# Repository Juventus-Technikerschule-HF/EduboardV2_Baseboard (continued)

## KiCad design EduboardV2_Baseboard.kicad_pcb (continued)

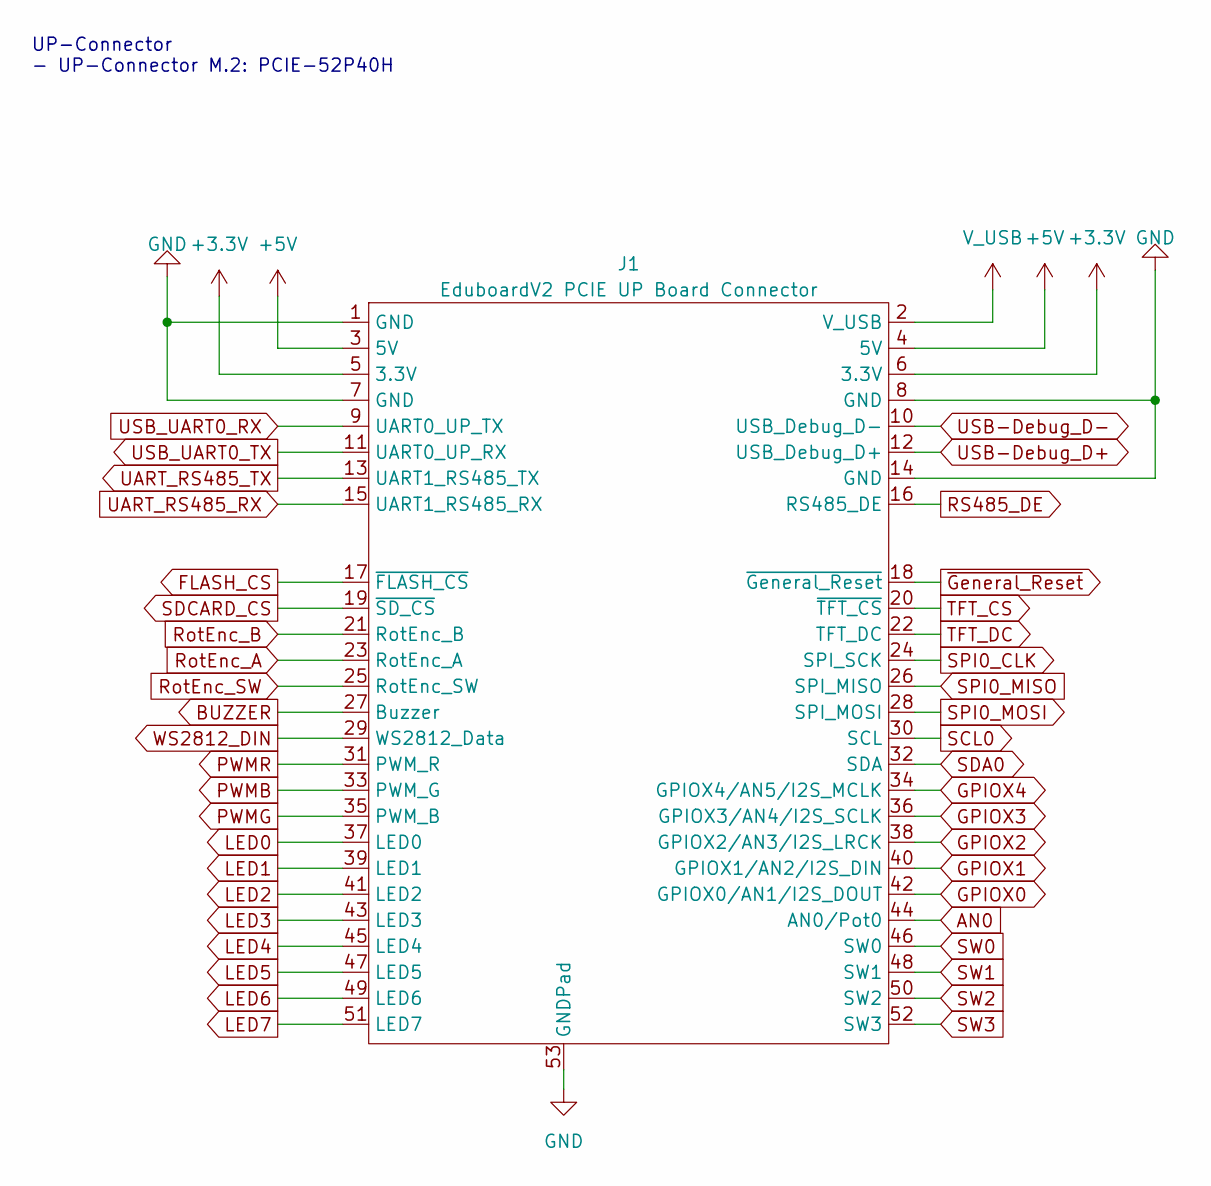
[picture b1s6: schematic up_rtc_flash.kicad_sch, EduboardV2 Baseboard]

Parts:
J1: EduboardV2 PCIE UP Board Connector; CONN-SMD_52P-P0.80-V_91304-70-052RXXX

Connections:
+5V: J1.3 (5V), J1.4 (5V); also elsewhere on the board
AN0: J1.44 (AN0/Pot0); also elsewhere on the board
BUZZER: J1.27 (Buzzer); also elsewhere on the board
FLASH_CS: J1.17 (~FLASH_CS); also elsewhere on the board
GPIOX0: J1.42 (GPIOX0/AN1/I2S_DOUT); also elsewhere on the board
GPIOX1: J1.40 (GPIOX1/AN2/I2S_DIN); also elsewhere on the board
GPIOX2: J1.38 (GPIOX2/AN3/I2S_LRCK); also elsewhere on the board
GPIOX3: J1.36 (GPIOX3/AN4/I2S_SCLK); also elsewhere on the board
GPIOX4: J1.34 (GPIOX4/AN5/I2S_MCLK); also elsewhere on the board
LED0: J1.37 (LED0); also elsewhere on the board
LED1: J1.39 (LED1); also elsewhere on the board
LED2: J1.41 (LED2); also elsewhere on the board
LED3: J1.43 (LED3); also elsewhere on the board
LED4: J1.45 (LED4); also elsewhere on the board
LED5: J1.47 (LED5); also elsewhere on the board
LED6: J1.49 (LED6); also elsewhere on the board
LED7: J1.51 (LED7); also elsewhere on the board
PWMB: J1.33 (PWM_G); also elsewhere on the board
PWMG: J1.35 (PWM_B); also elsewhere on the board
PWMR: J1.31 (PWM_R); also elsewhere on the board
RS485_DE: J1.16 (RS485_DE); also elsewhere on the board
RotEnc_A: J1.23 (RotEnc_A); also elsewhere on the board
RotEnc_B: J1.21 (RotEnc_B); also elsewhere on the board
RotEnc_SW: J1.25 (RotEnc_SW); also elsewhere on the board
SCL0: J1.30 (SCL); also elsewhere on the board
SDA0: J1.32 (SDA); also elsewhere on the board
SDCARD_CS: J1.19 (~SD_CS); also elsewhere on the board
SPI0_MISO: J1.26 (SPI_MISO); also elsewhere on the board
SPI0_MOSI: J1.28 (SPI_MOSI); also elsewhere on the board
SW0: J1.46 (SW0); also elsewhere on the board
SW1: J1.48 (SW1); also elsewhere on the board
SW2: J1.50 (SW2); also elsewhere on the board
SW3: J1.52 (SW3); also elsewhere on the board
TFT_CS: J1.20 (~TFT_CS); also elsewhere on the board
TFT_DC: J1.22 (TFT_DC); also elsewhere on the board
UART_RS485_RX: J1.15 (UART1_RS485_RX); also elsewhere on the board
UART_RS485_TX: J1.13 (UART1_RS485_TX); also elsewhere on the board
USB-Debug_D+: J1.12 (USB_Debug_D+); also elsewhere on the board
USB-Debug_D-: J1.10 (USB_Debug_D-); also elsewhere on the board
USB_UART0_TX: J1.11 (UART0_UP_RX); also elsewhere on the board
V_USB: J1.2 (V_USB); also elsewhere on the board
WS2812_DIN: J1.29 (WS2812_Data); also elsewhere on the board
~General_Reset: J1.18 (~General_Reset); also elsewhere on the board

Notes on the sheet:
UP-Connector - UP-Connector M.2: PCIE-52P40H

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
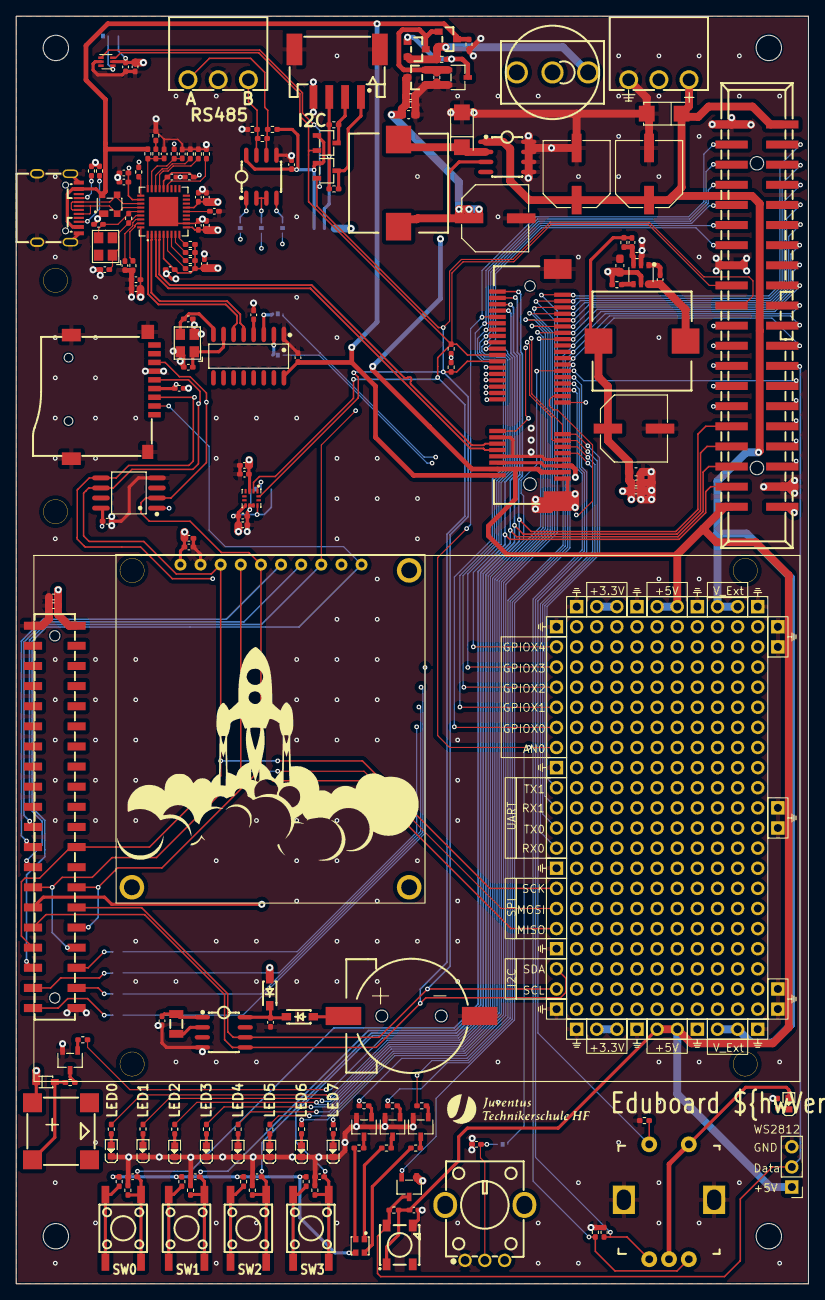
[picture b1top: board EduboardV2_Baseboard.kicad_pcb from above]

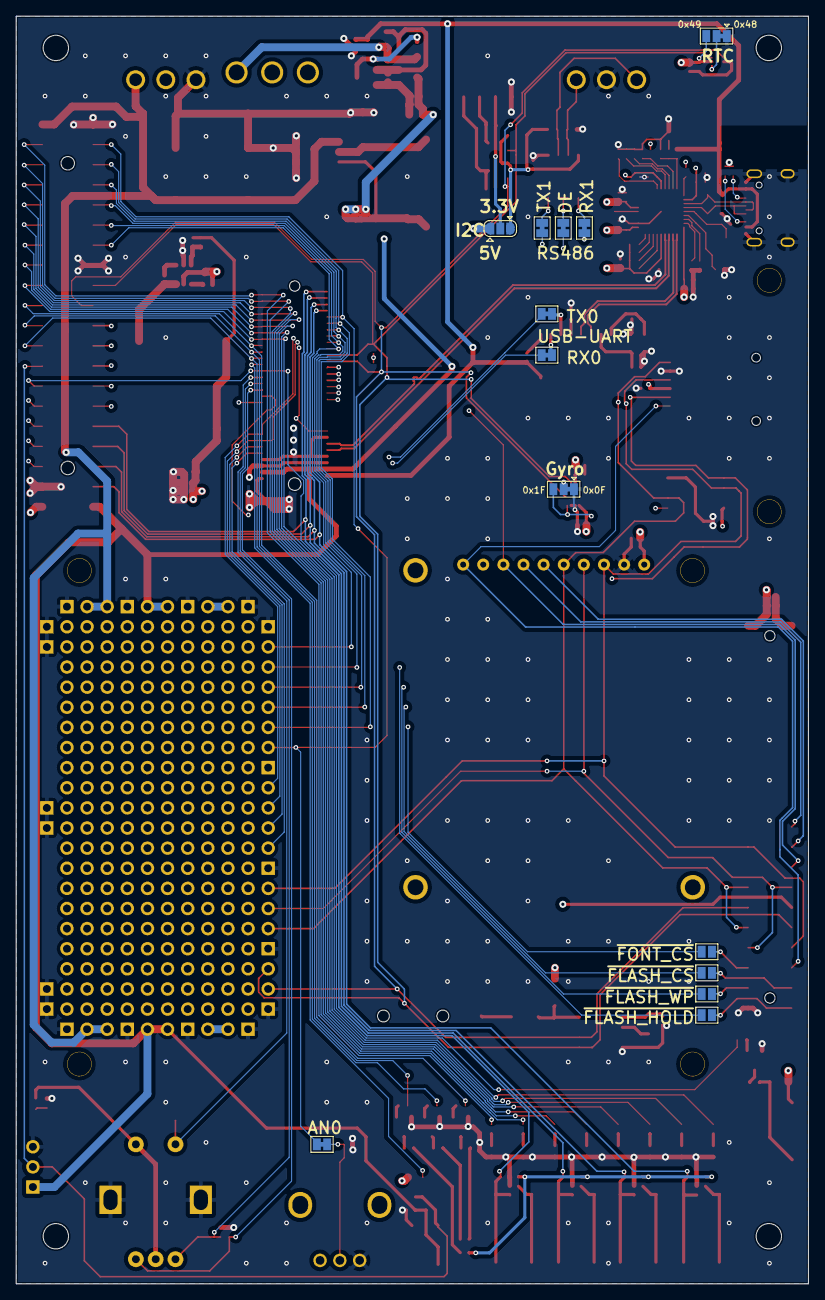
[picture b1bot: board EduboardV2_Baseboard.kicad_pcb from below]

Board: 4 copper layers, 100.0 x 160.0 mm, 189 parts (13 on the bottom side), 129 nets.

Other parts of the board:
C33, C35, C37, C39, C47, C49, C51, C53, C55: 100nF; C_0402_1005Metric_Pad0.74x0.62mm_HandSolder
C34, C36, C38, C40, C48, C50, C52, C54, C56: 1uF; C_0402_1005Metric_Pad0.74x0.62mm_HandSolder
JP9: SolderJumper_2_Bridged; SolderJumper-2_P1.3mm_Bridged_Pad1.0x1.5mm
T4, T7, T8: AO3400A; SOT-23-3_L2.9-W1.6-P1.90-LS2.8-BR
X1: 32.768 kHz; FC-135R_L3.2-W1.5

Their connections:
AN0: JP9.2 (B); also elsewhere on the board
unnamed 80: T7.3 (D); also elsewhere on the board
unnamed 81: T8.3 (D); also elsewhere on the board
SCL0: T7.2 (S); also elsewhere on the board
SDA0: T8.2 (S); also elsewhere on the board
WS2812_DIN: T4.2 (S); also elsewhere on the board
WS2812_DOUT: T4.3 (D); also elsewhere on the board

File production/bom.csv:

Designator,Footprint,Quantity,Value,LCSC Part #
BUZZER2,BUZ-SMD_4P-L8.5-W8.5-P8.50-BR,1,MLT-8530,
C1,0402,1,10pF,CL05C100JB5NNNC
C10,0603,1,"10uF, X5R, 25V",CL10A106MA8NRNC
C11,0402,1,"100nF, 50V",CL05B104KB54PNC
C12,0402,1,"1uF, 25V",CL05A105KA5NQNC
C13,0603,1,"10uF, X5R, 25V",CL10A106MA8NRNC
C14,0402,1,"100nF, 50V",CL05B104KB54PNC
C15,0402,1,"1uF, 25V",CL05A105KA5NQNC
"C16, C21, C5, C9",CAP-SMD_BD8.0-L8.3-W8.3-RD,4,"220uF, 35V",VEJ221M1VTR-0810
C17,0402,1,1nF,0402B102K500NT
C18,0402,1,10nF,CL05B103KB5NNNC
C19,0402,1,100nF,CL05B104KB54PNC
C2,0402,1,1uF,CL05A105KA5NQNC
C20,0402,1,10nF,CL05B103KB5NNNC
C22,0402,1,10nF,CL05B103KB5NNNC
C23,0402,1,100nF,CL05B104KB54PNC
C24,0402,1,10nF,CL05B103KB5NNNC
C25,0402,1,100nF,CL05B104KB54PNC
C26,0402,1,1uF,CL05A105KA5NQNC
C27,0402,1,1uF,CL05A105KA5NQNC
C28,0402,1,"100nF, 50V",CL05B104KB54PNC
C29,0402,1,22pF,0402CG220J500NT
C3,0402,1,10nF,CL05B103KB5NNNC
C30,0402,1,22pF,0402CG220J500NT
C31,0402,1,100nF,CL05B104KB54PNC
C32,0402,1,"100nF, 50V",CL05B104KB54PNC
C33,0402,1,100nF,CL05B104KB54PNC
C34,0402,1,1uF,CL05A105KA5NQNC
C35,0402,1,100nF,CL05B104KB54PNC
C36,0402,1,1uF,CL05A105KA5NQNC
C37,0402,1,100nF,CL05B104KB54PNC
C38,0402,1,1uF,CL05A105KA5NQNC
C39,0402,1,100nF,CL05B104KB54PNC
C4,0402,1,100nF,CL05B104KB54PNC
C40,0402,1,1uF,CL05A105KA5NQNC
C41,0402,1,"100nF, 50V",CL05B104KB54PNC
C42,0402,1,CL05C100JB5NNNC,CL05C100JB5NNNC
C43,0402,1,"100nF, 50V",CL05B104KB54PNC
C44,0402,1,CL05C100JB5NNNC,CL05C100JB5NNNC
C45,0402,1,"100nF, 50V",CL05B104KB54PNC
C46,0402,1,"100nF, 50V",CL05B104KB54PNC
C47,0402,1,100nF,CL05B104KB54PNC
C48,0402,1,1uF,CL05A105KA5NQNC
C49,0402,1,100nF,CL05B104KB54PNC
C50,0402,1,1uF,CL05A105KA5NQNC
C51,0402,1,100nF,CL05B104KB54PNC
C52,0402,1,1uF,CL05A105KA5NQNC
C53,0402,1,100nF,CL05B104KB54PNC
C54,0402,1,1uF,CL05A105KA5NQNC
C55,0402,1,100nF,CL05B104KB54PNC
C56,0402,1,1uF,CL05A105KA5NQNC
C6,0402,1,"100nF, 50V",CL05B104KB54PNC
C7,0603,1,"10uF, X5R, 25V",CL10A106MA8NRNC
C8,0402,1,22pF,0402CG220J500NT
"D1, D2",SOD-123_L2.7-W1.6-LS3.7-RD-1,2,B5819W_C8598,B5819W_C8598
"D10, D11, D12, D13, D5, D6, D7, D8, D9",LED0603-FD_BLUE,9,blue,19-217/BHC-ZL1M2RY/3T
D14,LED-SMD_FM-B2020RGBA-HG,1,RGB-LED,FM-B2020RGBA-HG
D15,LED-SMD_4P-L5.0-W5.0-TL_WS2812B-B,1,WS2812B-B_W,WS2812B-B/W
D16,SOD-323_L1.8-W1.3-LS2.5-RD,1,1N4148WST4,1N4148WS T4
D17,SOT-143-4_L2.9-W1.3-P1.92-LS2.4-BL,1,PRTR5V0U2X_C2827688,
"D3, D4",SMA_L4.3-W2.6-LS5.2-RD,2,SS210,SS210
IC1,SOIC-8_L5.0-W4.0-P1.27-LS6.0-BL,1,"PCF8563T_5,518","PCF8563T/5,518"
IC10,TQFN-36_L6.0-W6.0-P0.50-BL-EP3.7,1,USB2514BI-AEZG-TR,USB2514BI-AEZG-TR
IC2,SOIC-8_L5.3-W5.3-P1.27-LS8.0-BL,1,W25Q128JVSIQTR,W25Q128JVSIQTR
IC3,SOIC-8_L5.0-W4.0-P1.27-LS6.0-BL,1,XL1509-5.0E1,XL1509-5.0E1
IC4,TSOT-23-6_L2.9-W1.6-P0.95-LS2.8-BR,1,SY8113BADC,SY8113BADC
IC5,SOIC-8_L5.0-W4.0-P1.27-LS6.0-BL,1,SP3485EN-L_TR,SP3485EN-L/TR
IC8,LGA-12_L2.0-W2.0-P0.50-TR,1,STK8321,STK8321
J1,CONN-SMD_52P-P0.80-V_91304-70-052RXXX,1,EduboardV2 PCIE UP Board Connector,
JP1,SolderJumper-3_P1.3mm_Open_RoundedPad1.0x1.5mm,1,Stemma Voltage Selector,
"JP10, JP11, JP12, JP13",SolderJumper-2_P1.3mm_Open_Pad1.0x1.5mm,4,SolderJumper_2_Open,
"JP2, JP3",SolderJumper-3_P1.3mm_Bridged12_Pad1.0x1.5mm,2,SolderJumper_3_Bridged12,
"JP4, JP5, JP6, JP7, JP8, JP9",SolderJumper-2_P1.3mm_Bridged_Pad1.0x1.5mm,6,SolderJumper_2_Bridged,
"L1, L2",IND-SMD_L12.5-W12.5_SLF12565T,2,SLF12565T-680M2R0-PF,
"Q1, Q3, Q4",SOT-23_L2.9-W1.3-P1.90-LS2.4-BR,3,AO3401A,AO3401A
"Q2, T1, T2, T3, T4, T5, T7, T8",SOT-23-3_L2.9-W1.6-P1.90-LS2.8-BR,8,AO3400A,AO3400A
R1,0402,1,10k,0402WGF100JTCE
R10,0402,1,1k,0402WGF1001TCE
R11,0402,1,10k,0402WGF1002TCE
R12,0402,1,1k,0402WGF1001TCE
R13,RES-TH_RK09K1130AAU,1,50k,RK09K1130ACL
R14,0402,1,1k,0402WGF1001TCE
R15,0402,1,1k,0402WGF1001TCE
R16,0402,1,1k,0402WGF1001TCE
R17,0402,1,1k,0402WGF1001TCE
R18,0402,1,10k,0402WGF1002TCE
R19,0402,1,1k,0402WGF1001TCE
R2,0402,1,10k,0402WGF100JTCE
R21,0402,1,1k,0402WGF1001TCE
R22,0402,1,1k,0402WGF1001TCE
R23,0402,1,1k,0402WGF1001TCE
R25,0402,1,1k,0402WGF1001TCE
R26,0402,1,10k,0402WGF1002TCE
R27,0402,1,150R,0402WGF1500TCE
R28,0402,1,150R,0402WGF1500TCE
R29,0402,1,1k,0402WGF1001TCE
R3,0402,1,1M,0402WGF1003TCE
R30,0402,1,10k,0402WGF1002TCE
R31,0402,1,150R,0402WGF1500TCE
R32,0402,1,10R,0402WGF100JTCE
R33,0402,1,10R,0402WGF100JTCE
R34,0402,1,10R,0402WGF100JTCE
R35,0402,1,10k,0402WGF100JTCE
R36,0402,1,10k,0402WGF100JTCE
R37,0402,1,10k,0402WGF100JTCE
R38,0402,1,10k,0402WGF100JTCE
R39,0402,1,10R,0402WGF100JTCE
R4,0402,1,1M,0402WGF1003TCE
R40,0402,1,10R,0402WGF100JTCE
R49,0402,1,5.1k,0402WGF5101TCE
R5,0402,1,1M,0402WGF1003TCE
R50,0402,1,5.1k,0402WGF5101TCE
R51,0402,1,10k,0402WGF100JTCE
R52,0402,1,10k,0402WGF100JTCE
R53,0402,1,10k,0402WGF1002TCE
R54,0402,1,120R,0402WGF1200TCE
R55,0402,1,10k,0402WGF1002TCE
R6,0402,1,100k,0402WGF1003TCE
R60,0402,1,10k,0402WGF1002TCE
R61,0402,1,10k,0402WGF1002TCE
R62,0402,1,10k,0402WGF1002TCE
R63,0402,1,10k,0402WGF1002TCE
R64,0402,1,1M,
R65,0402,1,12k,
R66,0402,1,47k,
R67,0402,1,47k,
R68,0402,1,47k,
R69,0402,1,47k,
R7,0402,1,22k,0402WGF2202TCE
R70,0402,1,100k,0402WGF1003TCE
R71,0402,1,100k,0402WGF1003TCE
R72,0402,1,100k,0402WGF1003TCE
R73,0402,1,12k,
R8,0402,1,100k,0402WGF1003TCE
R9,0402,1,1k,0402WGF1001TCE
SW1,SW-TH_1FS1T1B9M2RES-5,1,1FS1T1B9M2RES-5,1FS1T1B9M2RES-5
"SW2, SW3, SW4, SW5",KEY-SMD_4P-L6.0-W6.0-P4.50-LS9.5-BL,4,K2-1102SP-C4SC-04,
SW6,SW-TH_PEC11R-4220F-S0012,1,PEC11R-4220F-S0012,PEC11R-4220F-S0012
U1,SOT-563,1,TMP112xxDRL,
X1,FC-135R_L3.2-W1.5,1,32.768 kHz,Q13FC1350000400
X10,CONN-SMD_S4B-PH-SM4-K-TB-LF-SN,1,S4B-PH-SM4-K-TB(LF)(SN),S4B-PH-SM4-K-TB(LF)(SN)
"X13, X4",CONN-TH_3P-P3.81_KF2EDGR-3.81-3P,2,KF2EDGR-3.81-3P,KF2EDGR-3.81-3P
X14,SOIC-16_L9.9-W3.9-P1.27-LS6.0-BL,1,CH340G,CH340G
X15,OSC-SMD_4P-L3.2-W2.5-BL,1,DSX321G 24MHz,
X2,BAT-SMD_CR1220-2ZX,1,CR1220-2ZX,CR1220-2ZX
X3,TF-SMD_TF-15-15,1,TF-15×15,TF-15×15
X7,IDC-SMD_BH-00105,1,BH-00105,BH-00105
X8,USB-C-SMD_TYPE-C-USB-17,1,USB3.1C16PFSMT,USB3.1C16PFSMT
X9,HDR-SMD_40P-P2.54-V-F-R2-C20-S7.1-EH,1,FH-00148,FH-00148
Y1,OSC-SMD_4P-L3.2-W2.5-BL,1,X322512MSB4SI,X322512MSB4SI

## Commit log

2022-06-05 initial commit. setup base-structure
2022-06-05 Add Library with lcsc components
2022-06-05 add comments/todos for each schematics page
2022-06-05 add gitignore and delete ignored data
2022-06-05 add kicad_prl file anyway, seams to have important info in it.
2022-06-06 updated library, partly created power.kicad_sch
2022-06-06 nearly finished display_ui.kicad_sch and power.kicad_sch
2022-06-06 added diode
2022-06-06 added up_rtc_flash.kicad_sch and finished others
2022-06-06 added more components
2022-06-07 beautified the library
2022-06-07 merged libraries and beautified the last symbols
2022-06-07 fixed RTC Symbol
2022-06-07 Rough pcb placement for space estimation. Exchanged 40P connector
2022-06-07 slight modifications
2022-06-08 changed pin types and fixed 3D-positions
2022-06-09 change all local labels to global labels.
2022-06-10 positioned components. Exchanged battery holder
2022-06-11 add PRTR5V0U2X USB ESD Protection to library
2022-06-11 move USB Serial Converter and USB Connector to correct pages
2022-06-11 move IMU to interfaces page
2022-06-11 add USB ESD Protection
2022-06-11 add WS2812 Output Connector and add Level shifter to WS2812 input for 3.3V->5V conversion
2022-06-11 move Audio-Connectors to connectors page
2022-06-11 move RS485 Connector to connectors page
2022-06-11 add IRLML6402 P Channel Mosfet for more Power Capabilities
2022-06-11 add some autosave files...
2022-06-11 change voltage selector
2022-06-11 add stemma connector circuit
2022-06-11 fix Resistor Value for WS2812 level shifter
2022-06-11 add I2C0 Pullups
2022-06-11 reassign symbol references after page movements. Place in pcb
2022-06-11 fix power symbol problem.
2022-06-12 added rotary encoder
2022-06-12 Fix hole not showing in 3d. THT holes had paste enabled.
2022-06-12 add rotary encoder circuit
2022-06-12 Fix Power Label Mess.
    Add Single Power_Output Symbol to each Power Network. All other Power-Labels are Power_Inputs.
    ERC now shows no Power_Output/Input Errors.
2022-06-18 change rotary encoder signals to Outputs
2022-06-18 remove duplicate accelerometer
2022-06-18 Add Global Signals to UP page.
    Audio Out missing,
    USB Debug / USB Direct missing
2022-06-18 Something Something USB Connector?!
2022-06-19 Add 24MHz Quartz and some Resistors
2022-06-19 Add new Page for USB Hub circuit.
2023-03-14 migrate to kicad 7
2023-03-16 add tft touch controller info, work on mpcie pinout
2023-04-11 start rework of baseboard.
2023-04-16 rework schematic. remove unnescessary stuff. Connect PCIE Connector. Select new Temperature Sensor (I2C) Define Signals for 40Pin Connector
2023-04-16 replace display with better module, start layout parts on pcb.
2023-04-17 add protoboard area. not yet done
2023-04-18 Layout of parts done. Started laying tracks
2023-04-19 proceed with layout
2023-04-20 work on layout.
2023-04-20 layout done so far. Have to check everything again
2023-04-21 fix parts (like led were wrong way round) Neatify Board
2023-04-23 finalize baseboard. finishing touches
2023-04-24 remove some part designators from silkscreen
2023-04-25 ready for order first prototype
2023-05-15 mark errors found on first prototypes
2023-06-20 fix some wrong jlcpcb part numbers
2023-06-20 add 2x DAC and fix I2C Impedance and Level Shifter
2023-06-20 fix X6 holesize to 1mm. also make pads a bit larger
2023-06-20 change ws2812 level shifter to bsn20
2023-06-20 change version to 2.1
2023-06-20 replace some parts (levelshifter) and add dac's
2023-06-20 add dac signals to protoboard part
2023-06-20 add GND-Pin for convenience
2023-06-20 add pullup resistors to cs pins and change dac pins to gpiox0 and 1 (AN0 is connected to pot)
2023-06-20 set pwm channels to pull down
2023-06-20 work on layout with for v2.1
2023-06-22 rotate power switch 90degrees to prevent damage in shipping process
2023-06-22 change power switch fets to IRLML6402 and 2N7002
2023-06-22 Redo gnd layer and gnd via stitching
2023-06-22 add some part alternatives and create production data
2023-06-25 Sort out RX/TX problems, improve DAC Circuits, Improve Board Text, switch out certain solder-jumpers with resistors
2023-06-25 finalize data v2.1.
2023-06-26 Finalize Data and order V2.1
2023-06-27 add alternative for buzzer
2023-07-13 Add CPU and Display Clip 3D Models
2023-07-13 add new version of cpu and display clips
2023-07-14 add display alternatives
2023-10-30 replace DAC with SPI Variant. Set Version to 2.2
2024-07-12 migrate to kicad version 8. Add some alternative part numbers
2024-07-13 add alternative parts
